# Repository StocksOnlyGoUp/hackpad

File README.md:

# hackpad
Screenshot of hackpad

Screenshot of schematic

Screenshot of PCB

Screenshot of case

BOM
  1 3d printed top
  1 3d printed bottom
  1 pcb
  4 SK6812 MINI-E LEDs
  4 MX-Style switches
  1 XIAO RP2040
  4 M3x16mm screws
  4 M3x5mx4mm heatset inserts

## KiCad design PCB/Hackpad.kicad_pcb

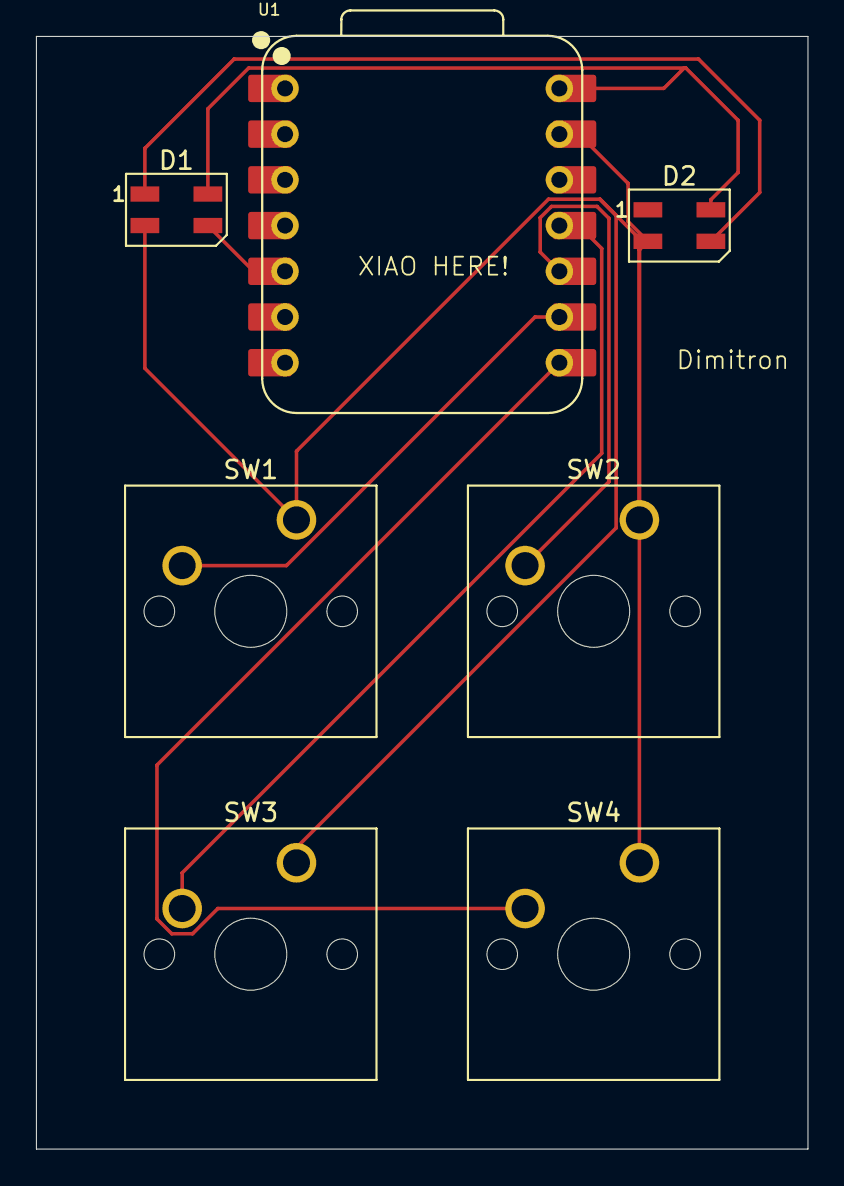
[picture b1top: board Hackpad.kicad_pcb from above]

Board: 2 copper layers, 42.9 x 61.8 mm, 7 parts (0 on the bottom side), 8 nets.

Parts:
D1, D2: SK6812MINI; LED_SK6812MINI_PLCC4_3.5x3.5mm_P1.75mm
SW1, SW2, SW3, SW4: SW_Push; SW_Cherry_MX_1.00u_PCB
U1: XIAO-RP2040-DIP

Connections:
+5V: D1.4 (VDD), D2.4 (VDD), U1.14 (VBUS)
GND: D1.2 (VSS), D2.2 (VSS), SW1.1, SW2.1, SW3.1, SW4.1, U1.13 (GND)
unnamed: D1.3 (DIN), U1.5 (GPIO6/SDA)
unnamed: D1.1 (DOUT), D2.3 (DIN)
unnamed: SW4.2, U1.8 (GPIO1/RX)
unnamed: SW1.2, U1.9 (GPIO2/SCK)
unnamed: SW3.2, U1.11 (GPIO3/MOSI)
unnamed: SW2.2, U1.10 (GPIO4/MISO)
